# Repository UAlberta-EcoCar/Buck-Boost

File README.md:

# Buck-Boost
Testing a buck boost controller

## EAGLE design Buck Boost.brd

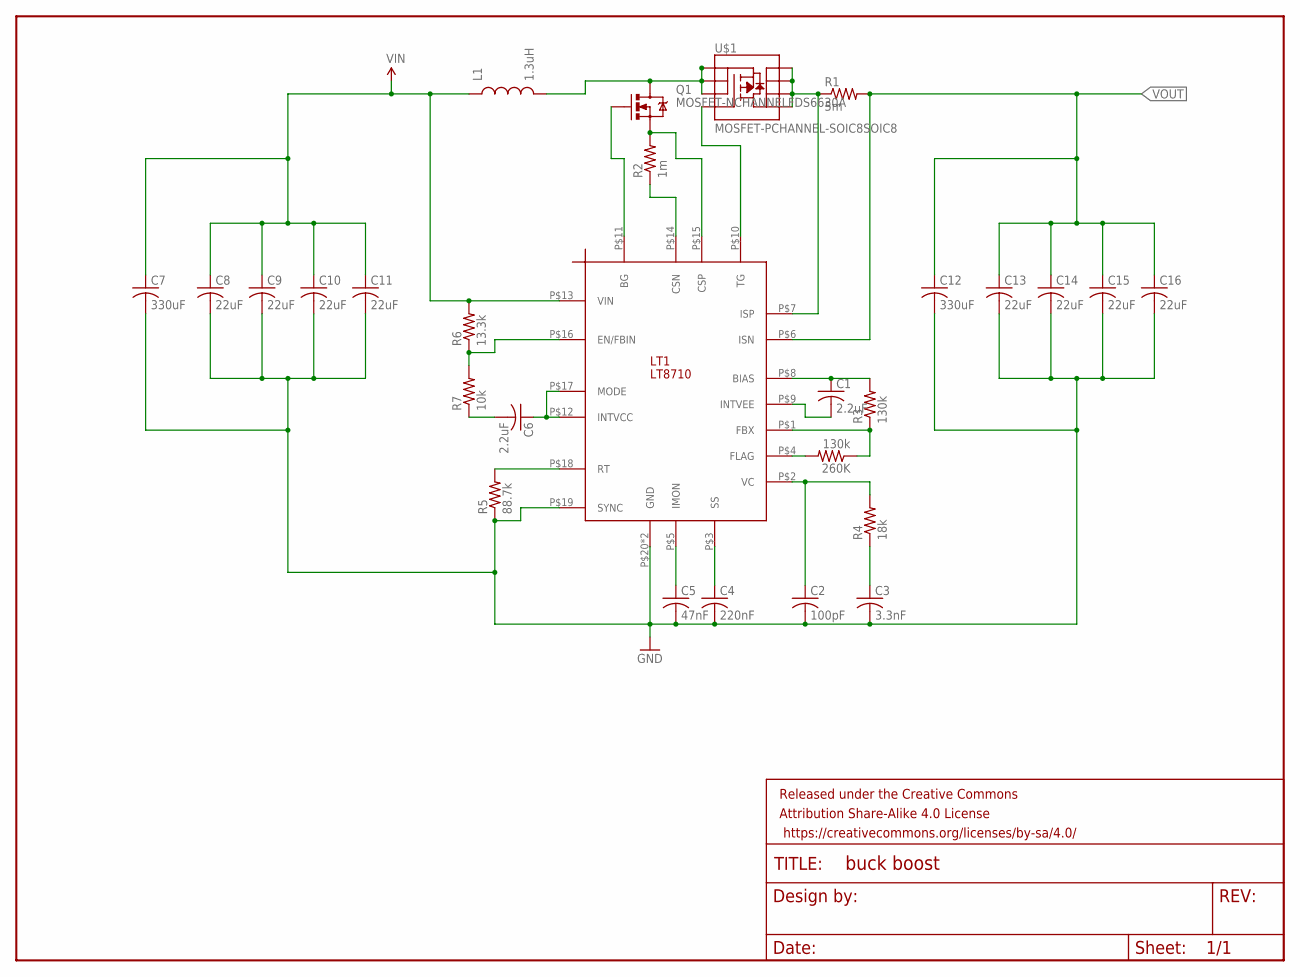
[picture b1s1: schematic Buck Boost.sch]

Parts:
260K: 130k; R1206
C1, C6: 2.2uF; C1206
C2: 100pF; C1206
C3: 3.3nF; C1206
C4: 220nF; C1206
C5: 47nF; C1206
C7, C12: 330uF; C4564
C8, C9, C10, C11, C13, C14, C15, C16: 22uF; C1206
FRAME1: FRAME-LETTERNO_PACKAGE; DUMMY
L1: 1.3uH; 1210
LT1: LT8710
Q1: MOSFET-NCHANNELFDS6630A; SO08
R1: 5m; R1206
R2: 1m; R1206
R3: 130k; R1206
R4: 18k; R1206
R5: 88.7k; R1206
R6: 13.3k; R1206
R7: 10k; R1206
U$1: MOSFET-PCHANNEL-SOIC8SOIC8; SO08

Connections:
GND: C2.2, C3.2, C4.2, C5.2, C7.2, C8.2, C9.2, C10.2, C11.2, C12.2, C13.2, C14.2, C15.2, C16.2, LT1.P$19 (SYNC), LT1.P$20 (GND), LT1.P$21 (GND), R5.1
unnamed: LT1.P$7 (ISP), R1.1, U$1.5 (D), U$1.6 (D), U$1.7 (D), U$1.8 (D)
unnamed: LT1.P$15 (CSP), Q1.1 (S), Q1.2 (S), Q1.3 (S), R2.2
unnamed: C1.1, LT1.P$8 (BIAS), R3.2
unnamed: C1.2, LT1.P$9 (INTVEE)
unnamed: 260K.1, LT1.P$1 (FBX), R3.1
unnamed: 260K.2, LT1.P$4 (FLAG)
unnamed: LT1.P$16 (EN/FBIN), R6.1, R7.2
unnamed: C6.2, R7.1
unnamed: C6.1, LT1.P$12 (INTVCC), LT1.P$17 (MODE)
unnamed: C3.1, R4.1
unnamed: LT1.P$18 (RT), R5.2
unnamed: C2.1, LT1.P$2 (VC), R4.2
unnamed: C4.1, LT1.P$3 (SS)
unnamed: C5.1, LT1.P$5 (IMON)
unnamed: LT1.P$14 (CSN), R2.1
unnamed: LT1.P$10 (TG), U$1.4 (G)
unnamed: LT1.P$11 (BG), Q1.4 (G)
unnamed: L1.2, Q1.5 (D), Q1.6 (D), Q1.7 (D), Q1.8 (D), U$1.1 (S), U$1.2 (S), U$1.3 (S)
VIN: C7.1, C8.1, C9.1, C10.1, C11.1, L1.1, LT1.P$13 (VIN), R6.2
VOUT: C12.1, C13.1, C14.1, C15.1, C16.1, LT1.P$6 (ISN), R1.2

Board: 2 copper layers, 29 parts (0 on the bottom side), 21 nets, no tracks yet.

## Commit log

2016-12-24 spice models working

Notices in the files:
parts and their libraries:
SparkFun-Aesthetics: Licensing: Creative Commons ShareAlike 4.0 International - https://creativecommons.org/licenses/by-sa/4.0
SparkFun-Aesthetics: Released under the Creative Commons Attribution Share-Alike 4.0 License
SparkFun-Aesthetics: https://creativecommons.org/licenses/by-sa/4.0
